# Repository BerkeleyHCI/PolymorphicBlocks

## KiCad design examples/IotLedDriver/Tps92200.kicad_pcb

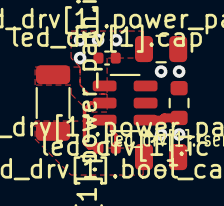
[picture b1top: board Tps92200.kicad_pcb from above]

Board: 2 copper layers, 7 parts (0 on the bottom side), 6 nets.

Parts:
led_drv[1].boot_cap: 16V 100nF X7R ±10% 0402 Multilayer Ceramic Capaci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; C_0402_1005Metric
led_drv[1].cap: 50V 100nF X7R ±10% 0402 Multilayer Ceramic Capaci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; C_0402_1005Metric
led_drv[1].ic: TPS92200D2DDCR; SOT-23-6
led_drv[1].power_path.in_cap: 50V 10uF X5R ±10% 0805 Multilayer Ceramic Capacit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; C_0805_2012Metric
led_drv[1].power_path.inductor: 980mA 4.7uH ±20% 320m? 1206 Inductors (SMD) ROHS; L_1206_3216Metric
led_drv[1].power_path.out_cap: X5R 25V ±10% 10uF 0805 Multilayer Ceramic Capacit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; C_0805_2012Metric
led_drv[1].rsense: ±1% 1/10W Thick Film Resistors 75V ±300ppm/? -55?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; R_0603_1608Metric

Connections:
Lgnd: led_drv[1].cap.2, led_drv[1].ic.3, led_drv[1].power_path.in_cap.2, led_drv[1].power_path.out_cap.2, led_drv[1].rsense.1
Lled_drv[1].boot_cap.neg: led_drv[1].boot_cap.2, led_drv[1].ic.5, led_drv[1].power_path.inductor.1
Lled_drv[1].boot_cap.pos: led_drv[1].boot_cap.1, led_drv[1].ic.6
Lled_drv[1].leda: led_drv[1].power_path.inductor.2, led_drv[1].power_path.out_cap.1
Lled_drv[1].ledk: led_drv[1].ic.1, led_drv[1].rsense.2
Lv12: led_drv[1].cap.1, led_drv[1].ic.4, led_drv[1].power_path.in_cap.1

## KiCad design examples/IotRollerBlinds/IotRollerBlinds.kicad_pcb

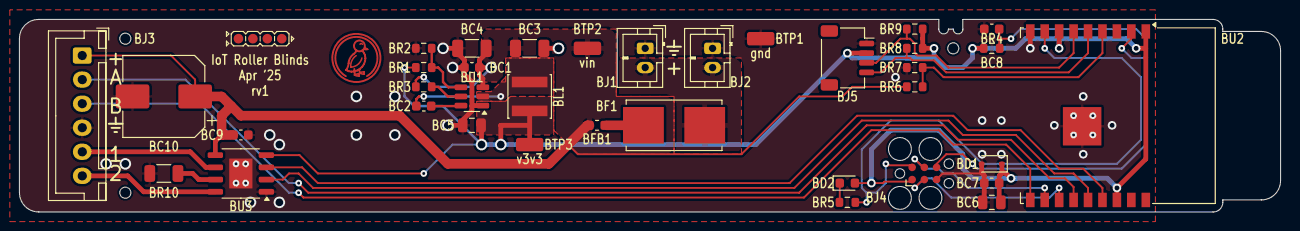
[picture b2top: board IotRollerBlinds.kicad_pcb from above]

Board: 2 copper layers, 131.0 x 20.0 mm, 40 parts (0 on the bottom side), 24 nets.

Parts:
BC1: reg_3v3.hf_in_cap; C_0603_1608Metric
BC2: reg_3v3.boot_cap; C_0603_1608Metric
BC3: reg_3v3.power_path.in_cap.c[0]; C_1206_3216Metric
BC4: reg_3v3.power_path.in_cap.c[1]; C_1206_3216Metric
BC5: reg_3v3.power_path.out_cap; C_0805_2012Metric
BC6: mcu.vcc_cap0; C_0805_2012Metric
BC7: mcu.vcc_cap1; C_0603_1608Metric
BC8: mcu.en_pull.c; C_0603_1608Metric
BC9: drv.vm_cap0; C_0603_1608Metric
BC10: drv.vm_cap1; CP_Elec_8x10
BD1: prot_3v3; D_SOD-323
BD2: ledr.package; LED_0603_1608Metric
BF1: fuse; Fuseholder_Littelfuse_Nano2_154x
BFB1: ferrite; L_0603_1608Metric
BH1: jlc_th.th1; JlcToolingHole_1.152mm
BH2: jlc_th.th2; JlcToolingHole_1.152mm
BH3: jlc_th.th3; JlcToolingHole_1.152mm
BJ1: pwr; JST_PH_B2B-PH-K_1x02_P2.00mm_Vertical
BJ2: pwr_out; JST_PH_B2B-PH-K_1x02_P2.00mm_Vertical
BJ3: conn; JST_XH_B6B-XH-A_1x06_P2.50mm_Vertical
BJ4: mcu.prog; Tag-Connect_TC2030-IDC-FP_2x03_P1.27mm_Vertical
BJ5: qwiic; JST_SH_SM04B-SRSS-TB_1x04-1MP_P1.00mm_Horizontal
BL1: reg_3v3.power_path.inductor; L_Sunlord_SWPA4030S
BR1: reg_3v3.fb.top_res; R_0603_1608Metric
BR2: reg_3v3.fb.bottom_res; R_0603_1608Metric
BR3: reg_3v3.en_res; R_0603_1608Metric
BR4: mcu.en_pull.r; R_0603_1608Metric
BR5: ledr.res; R_0603_1608Metric
BR6: vin_sense.top_res; R_0603_1608Metric
BR7: vin_sense.bottom_res; R_0603_1608Metric
BR8: qwiic_pull.scl_res; R_0603_1608Metric
BR9: qwiic_pull.sda_res; R_0603_1608Metric
BR10: drv.isen_res; R_1206_3216Metric
BTP1: gnd; TestPoint_TE_RCT_0805
BTP2: vin; TestPoint_TE_RCT_0805
BTP3: v3v3; TestPoint_TE_RCT_0805
BU1: reg_3v3.ic; SOT-23-6
BU2: mcu.ic; ESP-WROOM-02
BU3: drv.ic; HSOP-8-1EP_3.9x4.9mm_P1.27mm_EP2.41x3.1mm
duck: G***; Symbol_Duckling

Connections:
Bconn.enca: BJ3.2, BU2.13
Bconn.encb: BJ3.3, BU2.10
Bdrv.ic.isen: BR10.2, BU3.7
Bdrv.in1: BU2.15, BU3.3
Bdrv.in2: BU2.14, BU3.2
Bdrv.out1: BJ3.5, BU3.6
Bdrv.out2: BJ3.6, BU3.8
Bfuse.pwr_out: BF1.2, BFB1.1
Bgnd: BC1.2, BC3.2, BC4.2, BC5.2, BC6.2, BC7.2, BC8.2, BC9.2, BC10.2, BD1.2, BJ1.1, BJ2.1, BJ3.4, BJ4.5, BJ5.1, BR2.2, BR7.2, BR10.1, BTP1.1, BU1.1, BU2.9, BU2.19, BU3.1, BU3.9
Bledr.res.a: BD2.1, BR5.1
Bmcu.program_boot_node: BJ4.2, BR5.2, BU2.8
Bmcu.program_en_node: BC8.1, BJ4.6, BR4.2, BU2.2
Bmcu.program_uart_node.a_tx: BJ4.3, BU2.12
Bmcu.program_uart_node.b_tx: BJ4.4, BU2.11
Bqwiic_pull.i2c.scl: BJ5.4, BR8.2, BU2.5
Bqwiic_pull.i2c.sda: BJ5.3, BR9.2, BU2.6
Breg_3v3.boot_cap.neg: BC2.2, BL1.1, BU1.2
Breg_3v3.boot_cap.pos: BC2.1, BU1.6
Breg_3v3.en_res.b: BR3.2, BU1.5
Breg_3v3.fb.output: BR1.2, BR2.1, BU1.4
Bv3v3: BC5.1, BC6.1, BC7.1, BD1.1, BD2.2, BJ4.1, BJ5.2, BL1.2, BR1.1, BR4.1, BR8.1, BR9.1, BTP3.1, BU2.1, BU2.7, BU2.16, BU3.4
Bvin: BC1.1, BC3.1, BC4.1, BC9.1, BC10.1, BFB1.2, BJ3.1, BR3.1, BR6.1, BTP2.1, BU1.3, BU3.5
Bvin_raw: BF1.1, BJ1.2, BJ2.2
Bvin_sense.output: BR6.2, BR7.1, BU2.4

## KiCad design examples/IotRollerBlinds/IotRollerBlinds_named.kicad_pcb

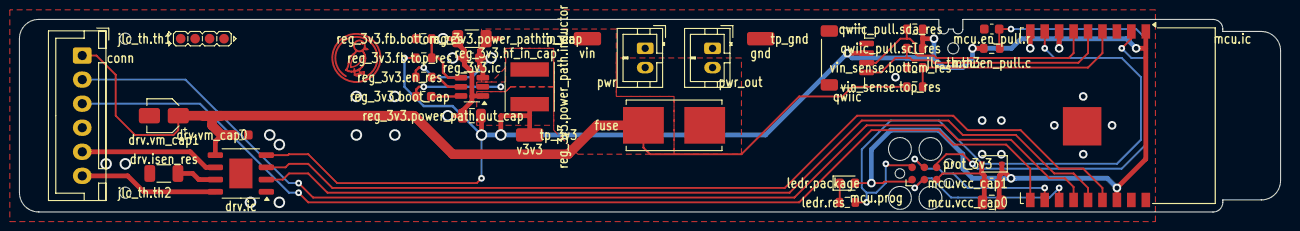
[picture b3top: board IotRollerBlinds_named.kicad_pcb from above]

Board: 2 copper layers, 131.0 x 20.0 mm, 38 parts (0 on the bottom side), 23 nets.

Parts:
conn: B6B-XH-A; JST_XH_B6B-XH-A_1x06_P2.50mm_Vertical
drv.ic: DRV8870DDAR; HSOP-8-1EP_3.9x4.9mm_P1.27mm_EP2.41x3.1mm
drv.isen_res: ±1% 1/4W Thick Film Resistors 200V ±800ppm/? -55?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; R_1206_3216Metric
drv.vm_cap0: 50V 100nF X7R ±10% 0603 Multilayer Ceramic Capaci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; C_0603_1608Metric
drv.vm_cap1: -40?~+105? 2000hrs@105? 47uF 5.4mm 35V 6.3mm ±20%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; CP_Elec_3x5.4
duck: G***; Symbol_Duckling
fuse: 01550900M; Fuseholder_Littelfuse_Nano2_154x
jlc_th.th1, jlc_th.th2, jlc_th.th3: JlcToolingHole_1.152mm
ledr.package: Red 615~630nm 1.9~2.2V 0603 Light Emitting Diodes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; LED_0603_1608Metric
ledr.res: ±1% 1/10W Thick Film Resistors 75V ±100ppm/? -55?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; R_0603_1608Metric
mcu.en_pull.c: 50V 1uF X5R ±10% 0603 Multilayer Ceramic Capacito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; C_0603_1608Metric
mcu.en_pull.r: ±1% 1/10W Thick Film Resistors 75V ±100ppm/? -55?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; R_0603_1608Metric
mcu.ic: ESP32-C3-WROOM-02; ESP-WROOM-02
mcu.prog: Tag-Connect_TC2030-IDC-FP_2x03_P1.27mm_Vertical
mcu.vcc_cap0: X5R 25V ±10% 10uF 0805 Multilayer Ceramic Capacit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; C_0805_2012Metric
mcu.vcc_cap1: 50V 100nF X7R ±10% 0603 Multilayer Ceramic Capaci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; C_0603_1608Metric
prot_3v3: 5?A@1V 90? Single 3.53V~3.67V 200mW 3.6V SOD-323 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; D_SOD-323
pwr: B2B-PH-K; JST_PH_B2B-PH-K_1x02_P2.00mm_Vertical
pwr_out: B2B-PH-K; JST_PH_B2B-PH-K_1x02_P2.00mm_Vertical
qwiic: SM04B-SRSS-TB; JST_SH_SM04B-SRSS-TB_1x04-1MP_P1.00mm_Horizontal
qwiic_pull.scl_res, qwiic_pull.sda_res: ±1% 1/10W Thick Film Resistors 75V ±100ppm/? -55?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; R_0603_1608Metric
reg_3v3.boot_cap, reg_3v3.hf_in_cap: 50V 100nF X7R ±10% 0603 Multilayer Ceramic Capaci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; C_0603_1608Metric
reg_3v3.en_res, reg_3v3.fb.bottom_res, reg_3v3.fb.top_res: ±1% 1/10W Thick Film Resistors 75V ±100ppm/? -55?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; R_0603_1608Metric
reg_3v3.ic: TPS54202H; SOT-23-6
reg_3v3.power_path.in_cap: 50V 10uF X5R ±10% 1206 Multilayer Ceramic Capacit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; C_1206_3216Metric
reg_3v3.power_path.inductor: 1.4A 22uH ±20% 126m? SMD Power Inductors ROHS; L_Taiyo-Yuden_NR-50xx
reg_3v3.power_path.out_cap: X5R 25V ±10% 10uF 0805 Multilayer Ceramic Capacit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; C_0805_2012Metric
tp_3v3: v3v3; TestPoint_TE_RCT_0805
tp_gnd: gnd; TestPoint_TE_RCT_0805
tp_vin: vin; TestPoint_TE_RCT_0805
vin_sense.bottom_res, vin_sense.top_res: ±1% 1/10W Thick Film Resistors 75V ±100ppm/? -55?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; R_0603_1608Metric

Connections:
Bconn.enca: conn.2, mcu.ic.13
Bconn.encb: conn.3, mcu.ic.10
Bdrv.ic.isen: drv.ic.7, drv.isen_res.2
Bdrv.in1: drv.ic.3, mcu.ic.15
Bdrv.in2: drv.ic.2, mcu.ic.14
Bdrv.out1: conn.5, drv.ic.6
Bdrv.out2: conn.6, drv.ic.8
Bgnd: conn.4, drv.ic.1, drv.ic.9, drv.isen_res.1, drv.vm_cap0.2, drv.vm_cap1.2, mcu.en_pull.c.2, mcu.ic.9, mcu.ic.19, mcu.prog.5, mcu.vcc_cap0.2, mcu.vcc_cap1.2, prot_3v3.2, pwr.1, pwr_out.1, qwiic.1, reg_3v3.fb.bottom_res.2, reg_3v3.hf_in_cap.2, reg_3v3.ic.1, reg_3v3.power_path.in_cap.2, reg_3v3.power_path.out_cap.2, tp_gnd.1, vin_sense.bottom_res.2
Bledr.res.a: ledr.package.1, ledr.res.1
Bmcu.program_boot_node: ledr.res.2, mcu.ic.8, mcu.prog.2
Bmcu.program_en_node: mcu.en_pull.c.1, mcu.en_pull.r.2, mcu.ic.2, mcu.prog.6
Bmcu.program_uart_node.a_tx: mcu.ic.12, mcu.prog.3
Bmcu.program_uart_node.b_tx: mcu.ic.11, mcu.prog.4
Bqwiic_pull.i2c.scl: mcu.ic.5, qwiic.4, qwiic_pull.scl_res.2
Bqwiic_pull.i2c.sda: mcu.ic.6, qwiic.3, qwiic_pull.sda_res.2
Breg_3v3.boot_cap.neg: reg_3v3.boot_cap.2, reg_3v3.ic.2, reg_3v3.power_path.inductor.1
Breg_3v3.boot_cap.pos: reg_3v3.boot_cap.1, reg_3v3.ic.6
Breg_3v3.en_res.b: reg_3v3.en_res.2, reg_3v3.ic.5
Breg_3v3.fb.output: reg_3v3.fb.bottom_res.1, reg_3v3.fb.top_res.2, reg_3v3.ic.4
Bv3v3: drv.ic.4, ledr.package.2, mcu.en_pull.r.1, mcu.ic.1, mcu.ic.7, mcu.ic.16, mcu.prog.1, mcu.vcc_cap0.1, mcu.vcc_cap1.1, prot_3v3.1, qwiic.2, qwiic_pull.scl_res.1, qwiic_pull.sda_res.1, reg_3v3.fb.top_res.1, reg_3v3.power_path.inductor.2, reg_3v3.power_path.out_cap.1, tp_3v3.1
Bvin: conn.1, drv.ic.5, drv.vm_cap0.1, drv.vm_cap1.1, fuse.2, reg_3v3.en_res.1, reg_3v3.hf_in_cap.1, reg_3v3.ic.3, reg_3v3.power_path.in_cap.1, tp_vin.1, vin_sense.top_res.1
Bvin_raw: fuse.1, pwr.2, pwr_out.2
Bvin_sense.output: mcu.ic.4, vin_sense.bottom_res.1, vin_sense.top_res.2

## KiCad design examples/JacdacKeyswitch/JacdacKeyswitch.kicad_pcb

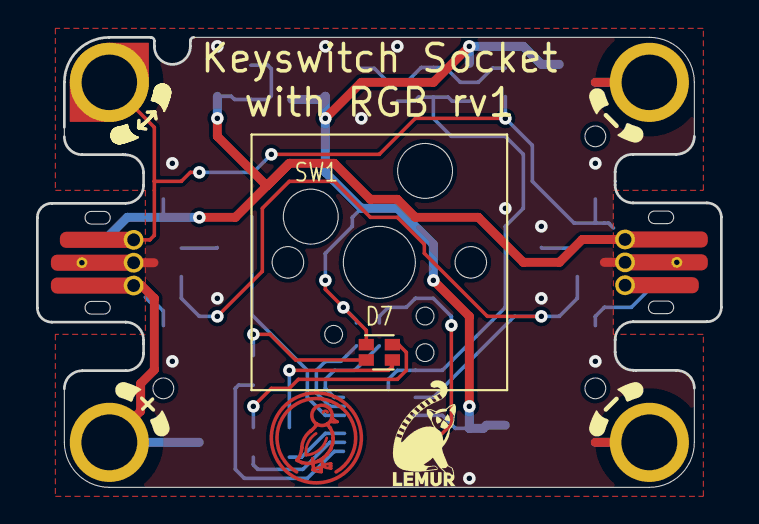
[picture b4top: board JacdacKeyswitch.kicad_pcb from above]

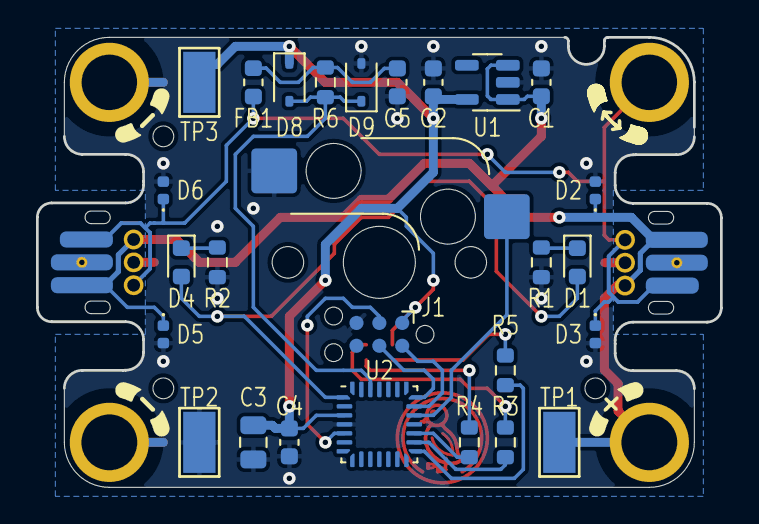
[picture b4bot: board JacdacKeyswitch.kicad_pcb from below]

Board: 2 copper layers, 38.0 x 25.0 mm, 39 parts (26 on the bottom side), 19 nets.

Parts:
C1, C2, C4, C5: C_0603_1608Metric
C3: C_0805_2012Metric
D1, D4: LED_0603_1608Metric
D2, D3, D5, D6: D_0402_1005Metric
D7: EAST1616RGBB2 (Everlight Electronics Co Ltd); LED_LiteOn_LTST-C19HE1WT
D8, D9: 1N5819WS (Guangdong Hottech) - 40V 600mV@1A 1A SO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; D_SOD-323
EC1, EC2: JD-PEC-02_Prerouted_recessed
FB1: L_0603_1608Metric
H1, H2, H3: JlcToolingHole_1.152mm
J1: Tag-Connect_TC2030-IDC-NL_2x03_P1.27mm_Vertical
MH1: jacdac_hole_DATA_notched_MH1
MH2: jacdac_hole_GND_MH2
MH3: jacdac_hole_PWR_MH3
MH4: jacdac_hole_GND_MH4
R1, R2, R3, R4, R5, R6: R_0603_1608Metric
SW1: PG151101S11 (Kailh); SW_Hotswap_Kailh_MX
TP1: 5015 (Keystone) - jd_pwr; TestPoint_Keystone_5015_Micro-Minature
TP2: 5015 (Keystone) - gnd; TestPoint_Keystone_5015_Micro-Minature
TP3: 5015 (Keystone) - v3v3; TestPoint_Keystone_5015_Micro-Minature
U1: XC6209F332MR-G (Torex Semiconductor Ltd); SOT-23-5
U2: STM32G031Gxxx (STMicroelectronics); QFN-28_4x4mm_P0.5mm
duck: G***; Symbol_Duckling
svg2mod: G***; Symbol_LemurSmall

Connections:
edge2.status_led.res.a: D4.1, R2.1
edge.status_led.res.a: D1.1, R1.1
gnd: C1.2, C2.2, C3.2, C4.2, C5.2, D2.2, D3.2, D5.2, D6.2, D9.2, EC1.2, EC2.2, J1.5, MH2.MH2, MH4.MH4, R1.2, R2.2, SW1.2, TP2.1, U1.2, U2.4
jd_data.jd_data: D3.1, D6.1, EC1.1, EC2.1, FB1.1, MH1.MH1
jd_if.ferrite.b: C5.1, FB1.2, R6.2
jd_if.signal: D8.2, D9.1, R6.1, U2.26
jd_pwr: C1.1, D2.1, D5.1, EC1.3, EC2.3, MH3.MH3, TP1.1, U1.1, U1.3
jd_status: D1.2, D4.2, U2.1
mcu.reset_node: J1.3, U2.5
mcu.swd_node.swclk: J1.4, U2.21
mcu.swd_node.swdio: J1.2, U2.20
rgb.blue_res.a: D7.1, R5.1
rgb.green_res.a: D7.4, R4.1
rgb.red_res.a: D7.3, R3.1
rgb.signals.blue: R5.2, U2.15
rgb.signals.green: R4.2, U2.17
rgb.signals.red: R3.2, U2.16
sw.out: SW1.1, U2.19
v3v3: C2.1, C3.1, C4.1, D7.2, D8.1, J1.1, TP3.1, U1.5, U2.3

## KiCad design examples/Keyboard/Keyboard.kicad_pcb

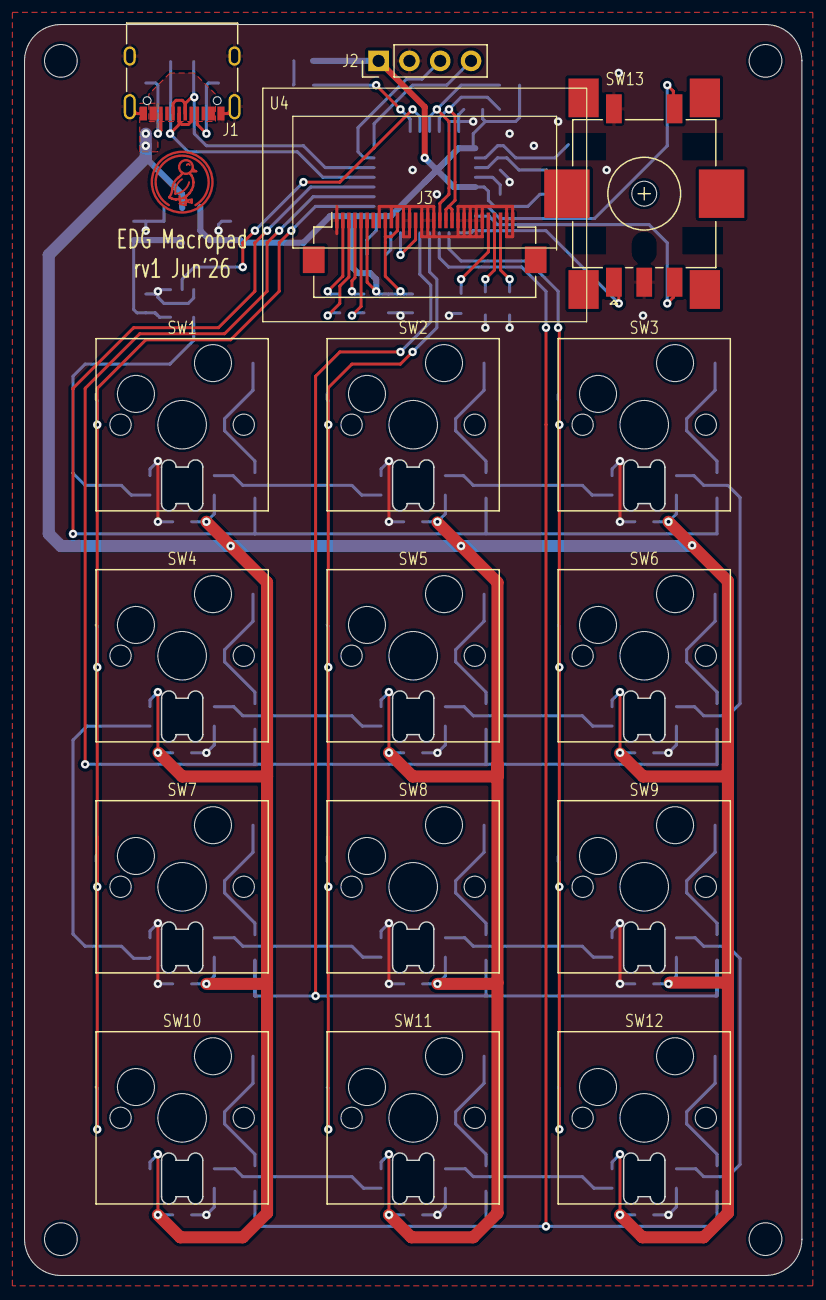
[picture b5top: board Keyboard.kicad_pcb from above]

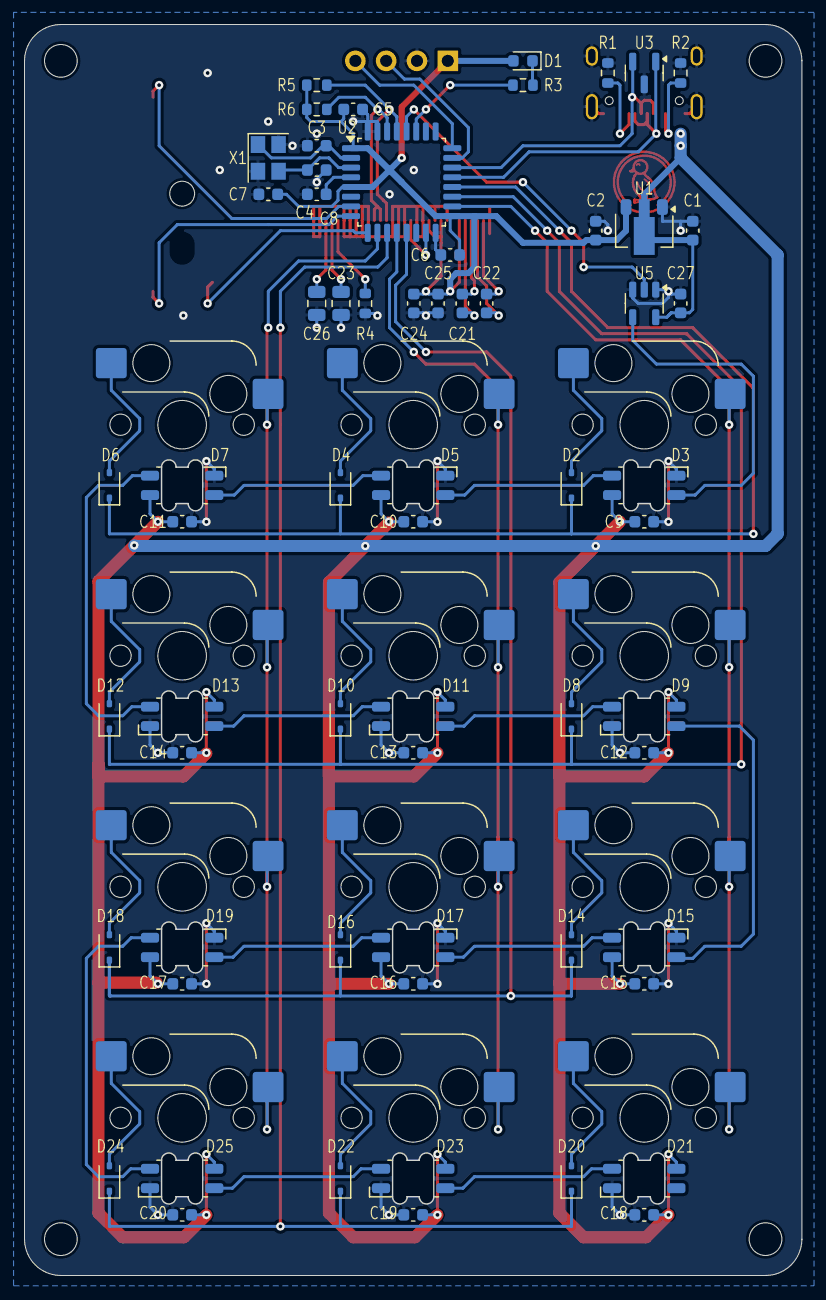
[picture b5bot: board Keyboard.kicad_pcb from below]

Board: 2 copper layers, 64.1 x 103.2 mm, 81 parts (51 on the bottom side), 59 nets.

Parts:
C1: reg.in_cap; C_0603_1608Metric
C2: reg.out_cap; C_0603_1608Metric
C3: mcu.crystal.cap_a; C_0603_1608Metric
C4: mcu.crystal.cap_b; C_0603_1608Metric
C5: mcu.vdd_cap[0]; C_0603_1608Metric
C6: mcu.vdd_cap[1]; C_0603_1608Metric
C7: mcu.vdda_cap; C_0603_1608Metric
C8: mcu.reset_cap; C_0603_1608Metric
C9: sw.sw[0,0].npx.cap; C_0603_1608Metric
C10: sw.sw[1,0].npx.cap; C_0603_1608Metric
C11: sw.sw[2,0].npx.cap; C_0603_1608Metric
C12: sw.sw[0,1].npx.cap; C_0603_1608Metric
C13: sw.sw[1,1].npx.cap; C_0603_1608Metric
C14: sw.sw[2,1].npx.cap; C_0603_1608Metric
C15: sw.sw[0,2].npx.cap; C_0603_1608Metric
C16: sw.sw[1,2].npx.cap; C_0603_1608Metric
C17: sw.sw[2,2].npx.cap; C_0603_1608Metric
C18: sw.sw[0,3].npx.cap; C_0603_1608Metric
C19: sw.sw[1,3].npx.cap; C_0603_1608Metric
C20: sw.sw[2,3].npx.cap; C_0603_1608Metric
C21: oled.c1_cap; C_0603_1608Metric
C22: oled.c2_cap; C_0603_1608Metric
C23: oled.vcomh_cap; C_0805_2012Metric
C24: oled.vdd_cap1; C_0603_1608Metric
C25: oled.vbat_cap; C_0603_1608Metric
C26: oled.vcc_cap; C_0805_2012Metric
C27: npx_shift.vdd_cap; C_0603_1608Metric
D1: ledr.package; LED_0603_1608Metric
D2: sw.sw[0,0].d; D_SOD-323
D3: sw.sw[0,0].npx.device; LED_SK6812MINI-E
D4: sw.sw[1,0].d; D_SOD-323
D5: sw.sw[1,0].npx.device; LED_SK6812MINI-E
D6: sw.sw[2,0].d; D_SOD-323
D7: sw.sw[2,0].npx.device; LED_SK6812MINI-E
D8: sw.sw[0,1].d; D_SOD-323
D9: sw.sw[0,1].npx.device; LED_SK6812MINI-E
D10: sw.sw[1,1].d; D_SOD-323
D11: sw.sw[1,1].npx.device; LED_SK6812MINI-E
D12: sw.sw[2,1].d; D_SOD-323
D13: sw.sw[2,1].npx.device; LED_SK6812MINI-E
D14: sw.sw[0,2].d; D_SOD-323
D15: sw.sw[0,2].npx.device; LED_SK6812MINI-E
D16: sw.sw[1,2].d; D_SOD-323
D17: sw.sw[1,2].npx.device; LED_SK6812MINI-E
D18: sw.sw[2,2].d; D_SOD-323
D19: sw.sw[2,2].npx.device; LED_SK6812MINI-E
D20: sw.sw[0,3].d; D_SOD-323
D21: sw.sw[0,3].npx.device; LED_SK6812MINI-E
D22: sw.sw[1,3].d; D_SOD-323
D23: sw.sw[1,3].npx.device; LED_SK6812MINI-E
D24: sw.sw[2,3].d; D_SOD-323
D25: sw.sw[2,3].npx.device; LED_SK6812MINI-E
J1: usb.conn; USB_C_Receptacle_XKB_U262-16XN-4BVC11
J2: mcu.sdi; PinHeader_1x04_P2.54mm_Vertical
J3: oled.device; Hirose_FH12-30S-0.5SH_1x30-1MP_P0.50mm_Horizontal
R1: usb.cc_pull.cc1; R_0603_1608Metric
R2: usb.cc_pull.cc2; R_0603_1608Metric
R3: ledr.res; R_0603_1608Metric
R4: oled.iref_res; R_0603_1608Metric
R5: i2c_pull.scl_res; R_0603_1608Metric
R6: i2c_pull.sda_res; R_0603_1608Metric
SW1: sw.sw[0,0].sw; SW_Hotswap_Kailh_MX
SW2: sw.sw[1,0].sw; SW_Hotswap_Kailh_MX
SW3: sw.sw[2,0].sw; SW_Hotswap_Kailh_MX
SW4: sw.sw[0,1].sw; SW_Hotswap_Kailh_MX
SW5: sw.sw[1,1].sw; SW_Hotswap_Kailh_MX
SW6: sw.sw[2,1].sw; SW_Hotswap_Kailh_MX
SW7: sw.sw[0,2].sw; SW_Hotswap_Kailh_MX
SW8: sw.sw[1,2].sw; SW_Hotswap_Kailh_MX
SW9: sw.sw[2,2].sw; SW_Hotswap_Kailh_MX
SW10: sw.sw[0,3].sw; SW_Hotswap_Kailh_MX
SW11: sw.sw[1,3].sw; SW_Hotswap_Kailh_MX
SW12: sw.sw[2,3].sw; SW_Hotswap_Kailh_MX
SW13: enc; RotaryEncoder_Bourns_PEC11S
U1: reg.ic; SOT-89-3
U2: mcu.ic; LQFP-32_7x7mm_P0.8mm
U3: usb_esd; SOT-23
U4: oled.lcd; Lcd_Er_Oled0.96_1.1_Outline
U5: npx_shift.ic; SOT-23-5
X1: mcu.crystal.package; Crystal_SMD_3225-4Pin_3.2x2.5mm
duck: G***; Symbol_Duckling

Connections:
enc.a: SW13.A, U2.9
enc.b: SW13.B, U2.8
enc.sw: SW13.S1, U2.7
ledr.package.k: D1.1, R3.1
ledr.signal: R3.2, U2.27
mcu.gpio.sw_col_0: SW1.1, SW4.1, SW7.1, SW10.1, U2.18
mcu.gpio.sw_col_1: SW2.1, SW5.1, SW8.1, SW11.1, U2.12
mcu.gpio.sw_col_2: SW3.1, SW6.1, SW9.1, SW12.1, U2.10
mcu.gpio.sw_row_0: D2.1, D4.1, D6.1, U2.20
mcu.gpio.sw_row_1: D8.1, D10.1, D12.1, U2.19
mcu.gpio.sw_row_2: D14.1, D16.1, D18.1, U2.13
mcu.gpio.sw_row_3: D20.1, D22.1, D24.1, U2.11
mcu.ic.nrst: C8.1, U2.4
mcu.ic.swclk: J2.4, U2.24
mcu.ic.swdio: J2.3, U2.23
mcu.xtal_node.xi: C3.1, U2.2, X1.1
mcu.xtal_node.xo: C4.1, U2.3, X1.3
npx_shift.input: U2.28, U5.2
oled.device.c1n: C21.2, J3.5
oled.device.c1p: C21.1, J3.4
oled.device.c2n: C22.2, J3.3
oled.device.c2p: C22.1, J3.2
oled.device.iref: J3.26, R4.2
oled.device.vcc: C26.1, J3.28
oled.device.vcomh: C23.1, J3.27
oled.i2c.scl: J3.18, R5.2, U2.29
oled.i2c.sda: J3.19, J3.20, R6.2, U2.30
oled.reset: J3.14, U2.15
reg.pwr_out: C2.1, C5.1, C6.1, C7.1, C24.1, C25.1, D1.2, J2.1, J3.6, J3.9, J3.11, R5.1, R6.1, U1.3, U2.1, U2.5, U2.17
sw.npx_din: D3.4, U5.4
sw.sw[0,0].npx_dout: D3.2, D5.4
sw.sw[0,0].sw.com: D2.2, SW1.2
sw.sw[0,1].npx_din: D9.4, D11.2
sw.sw[0,1].npx_dout: D9.2, D15.4
sw.sw[0,1].sw.com: D8.2, SW4.2
sw.sw[0,2].npx_dout: D15.2, D17.4
sw.sw[0,2].sw.com: D14.2, SW7.2
sw.sw[0,3].npx_din: D21.4, D23.2
sw.sw[0,3].sw.com: D20.2, SW10.2
sw.sw[1,0].npx_dout: D5.2, D7.4
sw.sw[1,0].sw.com: D4.2, SW2.2
sw.sw[1,1].npx_din: D11.4, D13.2
sw.sw[1,1].sw.com: D10.2, SW5.2
sw.sw[1,2].npx_dout: D17.2, D19.4
sw.sw[1,2].sw.com: D16.2, SW8.2
sw.sw[1,3].npx_din: D23.4, D25.2
sw.sw[1,3].sw.com: D22.2, SW11.2
sw.sw[2,0].npx_dout: D7.2, D13.4
sw.sw[2,0].sw.com: D6.2, SW3.2
sw.sw[2,1].sw.com: D12.2, SW6.2
sw.sw[2,2].npx_dout: D19.2, D25.4
sw.sw[2,2].sw.com: D18.2, SW9.2
sw.sw[2,3].sw.com: D24.2, SW12.2
usb.conn.cc.cc1: J1.A5, R1.2
usb.conn.cc.cc2: J1.B5, R2.2
usb.gnd: C1.2, C2.2, C3.2, C4.2, C5.2, C6.2, C7.2, C8.2, C9.2, C10.2, C11.2, C12.2, C13.2, C14.2, C15.2, C16.2, C17.2, C18.2, C19.2, C20.2, C23.2, C24.2, C25.2, C26.2, C27.2, D3.3, D5.3, D7.3, D9.3, D11.3, D13.3, D15.3, D17.3, D19.3, D21.3, D23.3, D25.3, J1.A1, J1.A12, J1.B1, J1.B12, J1.S1, J2.2, J3.1, J3.8, J3.10, J3.12, J3.13, J3.15, J3.16, J3.17, J3.21, J3.22, J3.23, J3.24, J3.25, J3.29, J3.30, R1.1, R2.1, R4.1, SW13.C, SW13.S2, U1.1, U2.16, U2.31, U2.32, U3.3, U5.1, U5.3, X1.2, X1.4
usb.pwr: C1.1, C9.1, C10.1, C11.1, C12.1, C13.1, C14.1, C15.1, C16.1, C17.1, C18.1, C19.1, C20.1, C27.1, D3.1, D5.1, D7.1, D9.1, D11.1, D13.1, D15.1, D17.1, D19.1, D21.1, D23.1, D25.1, J1.A4, J1.A9, J1.B4, J1.B9, U1.2, U5.5
usb.usb.dm: J1.A7, J1.B7, U2.21, U3.1
usb.usb.dp: J1.A6, J1.B6, U2.22, U3.2

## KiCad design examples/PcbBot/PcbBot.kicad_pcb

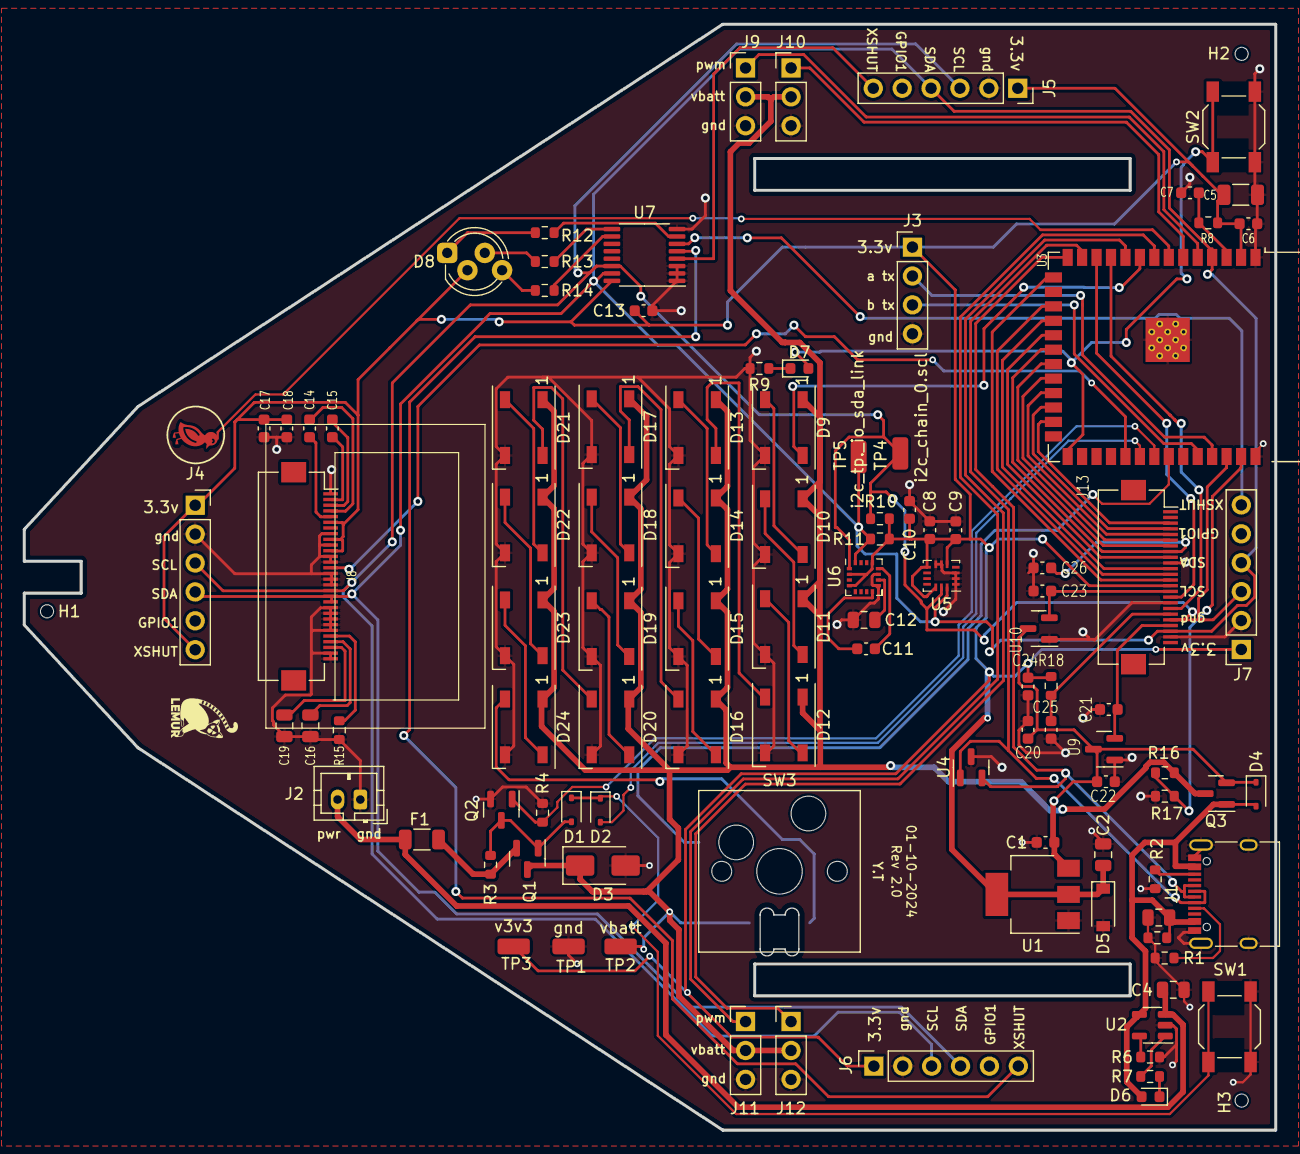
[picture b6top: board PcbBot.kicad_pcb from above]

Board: 2 copper layers, 110.0 x 97.2 mm, 109 parts (0 on the bottom side), 83 nets.

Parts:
C1, C6, C7, C8, C9, C10, C11, C13, C14, C15, C17, C18, C20, C21, C22, C23, C24, C25, C26: C_0603_1608Metric
C2, C3, C4, C12, C16, C19: C_0805_2012Metric
C5: C_1206_3216Metric
D1, D2: 30V 370mV@1mA 30mA SOD-323 Schottky Barrier Diode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; D_SOD-323
D3: 10?A@2V 5? Single 5.32V~5.92V 1W 5.6V SMAF Zener 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; D_SMA
D4: 40V 600mV@1A 1A SOD-323 Schottky Barrier Diodes (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; D_SOD-323
D5: 5?A@1V 90? Single 3.6V~3.8V 350mW 3.4V SOD-123 Ze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; D_SOD-123
D6: LED_0603_1608Metric
D7: Red 615~630nm 1.9~2.2V 0603 Light Emitting Diodes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; LED_0603_1608Metric
D8: COM-09264; LED_D5.0mm-4_RGB_Staggered_Pins
D9, D10, D11, D12, D13, D14, D15, D16, D17, D18, D19, D20, D21, D22, D23, D24: WS2812B; LED_WS2812B_PLCC4_5.0x5.0mm_P3.2mm
D25: SK6812MINI-E; LED_SK6812MINI-E
F1: 6V 2A 100A 4A 1206 Resettable Fuses ROHS; R_1206_3216Metric
H1, H2, H3: JlcToolingHole_1.152mm
J1: COM-15111; USB_C_Receptacle_XKB_U262-16XN-4BVC11
J2: B2B-PH-K; JST_PH_B2B-PH-K_1x02_P2.00mm_Vertical
J3: PinHeader2.54 1x4; PinHeader_1x04_P2.54mm_Vertical
J4, J5, J6, J7: PinSocket2.54 1x6; PinSocket_1x06_P2.54mm_Vertical
J8: AFC01-S30FCA-00; Hirose_FH12-30S-0.5SH_1x30-1MP_P0.50mm_Horizontal
J9, J10, J11, J12: PinHeader2.54 1x3; PinHeader_1x03_P2.54mm_Vertical
J13: AFC01-S24FCA-00; Hirose_FH12-24S-0.5SH_1x24-1MP_P0.50mm_Horizontal
Q1: 20V 3.1A 860mW 112m?@4.5V,2.8A 1V@250?A P Channel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; SOT-23
Q2: 60V 115mA 200mW 7.5?@10V,500mA 2.5V@250?A N Chann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; SOT-23
Q3: 30V 4A 44m?@10V,4.3A 1.4W 1.3V@250?A P Channel SO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; SOT-23
R1, R2, R3, R4, R5, R6, R7, R8, R9, R10, R11, R12, R13, R14, R15, R16, R17, R18: R_0603_1608Metric
SW1, SW2: 5.1mm switch; SW_SPST_SKQG_WithoutStem
SW3: PG151101S11; SW_Hotswap_Kailh_MX
TP1: gnd; TestPoint_TE_RCT_0805
TP2: vbatt; TestPoint_TE_RCT_0805
TP3: v3v3; TestPoint_TE_RCT_0805
TP4: i2c_chain_0.scl; TestPoint_TE_RCT_0805
TP5: i2c_tp._io_sda_link; TestPoint_TE_RCT_0805
U1: LDL1117S33R; SOT-223-3_TabPin2
U2: MCP73831T-2ACI/OT; SOT-23-5
U3: ESP32-S3-WROOM-1-N16R8; ESP32-S3-WROOM-1
U4: PESD5V0X1BT; SOT-23
U5: LSM6DS3TR-C; Bosch_LGA-14_3x2.5mm_P0.5mm
U6: QMC5883L; LGA-16_3x3mm_P0.5mm
U7: PCA9554APW,118; TSSOP-16_4.4x5mm_P0.65mm
U8: ER-OLED-0.96-1.1; Lcd_Er_Oled0.96_1.1_Outline
U9: XC6206P252MR; SOT-23
U10: XC6206P122MR-G; SOT-23
svg2mod: G***; Symbol_LemurSmall
svg2mod#2: G***; Symbol_DucklingSolid

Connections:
batt.pwr: C4.1, F1.1, J2.2, U2.3
batt_sense.output: R16.2, R17.1, U3.39
cam.device.reset: C25.1, J13.19, R18.2
cam.dvp8.href: J13.16, U3.12
cam.dvp8.pclk: C26.1, J13.8, U3.20
cam.dvp8.vsync: J13.18, U3.11
cam.dvp8.xclk: J13.12, U3.17
cam.dvp8.y0: J13.6, U3.22
cam.dvp8.y1: J13.4, U3.24
cam.dvp8.y2: J13.3, U3.25
cam.dvp8.y3: J13.5, U3.23
cam.dvp8.y4: J13.7, U3.21
cam.dvp8.y5: J13.9, U3.19
cam.dvp8.y6: J13.11, U3.18
cam.dvp8.y7: J13.13, U3.15
charge_led.res.a: D6.1, R7.1
charge_led.signal: R7.2, U2.1
charger.prog_res.a: R6.1, U2.5
expander.io.rgb_blue: R14.2, U7.10
expander.io.rgb_green: R13.2, U7.9
expander.io.rgb_red: R12.2, U7.7
expander.io.tof_xshut_1: J5.6, U7.4
expander.io.tof_xshut_2: J6.6, U7.5
expander.io.tof_xshut_3: J7.6, U7.6
fuse.pwr_out: F1.2, Q1.2, R3.1
gate.btn_out: D2.2, U3.32
gate.control: Q2.1, R4.2, U3.33
gate.ctl_diode.cathode: D1.1, D2.1, SW1.1
gate.pull_res.b: D1.2, Q1.1, Q2.3, R3.2
gnd: C1.2, C2.2, C3.2, C4.2, C5.2, C6.2, C7.2, C8.2, C9.2, C10.2, C12.2, C13.2, C16.2, C17.2, C18.2, C19.2, C20.2, C21.2, C22.2, C23.2, C24.2, C25.2, C26.2, D3.2, D5.2, D9.3, D10.3, D11.3, D12.3, D13.3, D14.3, D15.3, D16.3, D17.3, D18.3, D19.3, D20.3, D21.3, D22.3, D23.3, D24.3, D25.3, J1.A1, J1.A12, J1.B1, J1.B12, J1.S1, J2.1, J3.4, J4.2, J5.2, J6.2, J7.2, J8.1, J8.8, J8.10, J8.12, J8.13, J8.15, J8.16, J8.17, J8.21, J8.22, J8.23, J8.24, J8.25, J8.29, J8.30, J9.3, J10.3, J11.3, J12.3, J13.10, J13.17, J13.23, Q2.2, R1.1, R2.1, R4.1, R5.2, R6.2, R9.2, R15.2, R17.2, SW1.2, SW2.2, SW3.2, TP1.1, U1.1, U2.2, U3.1, U3.40, U3.41, U4.3, U5.1, U5.2, U5.3, U5.6, U5.7, U6.9, U6.11, U7.1, U7.2, U7.3, U7.8, U9.1, U10.1
i2c_chain_0.scl: J4.3, J5.3, J6.3, J7.3, J8.18, J13.20, R10.2, TP4.1, U3.38, U5.13, U6.1, U7.14
i2c_chain_0.sda: J4.4, J5.4, J6.4, J7.4, J8.19, J8.20, J13.22, R11.2, TP5.1, U3.4, U5.14, U6.16, U7.15
led.res.a: D7.1, R9.1
mag.c1.pos: C12.1, U6.10
mag.set_cap.neg: C11.2, U6.12
mag.set_cap.pos: C11.1, U6.8
mcu.program_boot_node: D7.2, SW2.1, U3.27
mcu.program_en_node: C7.1, R8.2, U3.3
mcu.program_uart_node.a_tx: J3.2, U3.37
mcu.program_uart_node.b_tx: J3.3, U3.36
npx.din: D9.4, U3.9
npx.dout: D24.2, D25.4
npx.led[0].dout: D9.2, D10.4
npx.led[1].dout: D10.2, D11.4
npx.led[2].dout: D11.2, D12.4
npx.led[3].dout: D12.2, D13.4
npx.led[4].dout: D13.2, D14.4
npx.led[5].dout: D14.2, D15.4
npx.led[6].dout: D15.2, D16.4
npx.led[7].dout: D16.2, D17.4
npx.led[8].dout: D17.2, D18.4
npx.led[9].dout: D18.2, D19.4
npx.led[10].dout: D19.2, D20.4
npx.led[11].dout: D20.2, D21.4
npx.led[12].dout: D21.2, D22.4
npx.led[13].dout: D22.2, D23.4
npx.led[14].dout: D23.2, D24.4
oled.c1_cap.neg: C14.2, J8.5
oled.c1_cap.pos: C14.1, J8.4
oled.c2_cap.neg: C15.2, J8.3
oled.c2_cap.pos: C15.1, J8.2
oled.device.vcc: C19.1, J8.28
oled.device.vcomh: C16.1, J8.27
oled.iref_res.a: J8.26, R15.1
oled.reset: J8.14, U3.31
pwr: C1.1, C20.1, C22.1, D4.1, Q3.2, U1.3, U9.3, U10.3
rgb.blue_res.a: D8.4, R14.1
rgb.green_res.a: D8.3, R13.1
rgb.red_res.a: D8.1, R12.1
servo[0].pwm: J9.1, U3.5
servo[1].pwm: J10.1, U3.6
servo[2].pwm: J11.1, U3.8
servo[3].pwm: J12.1, U3.10
switch.out: SW3.1, U3.34
usb.conn.A5: J1.A5, R1.2
usb.conn.B5: J1.B5, R2.2
usb_chain_0.d_N: J1.A7, J1.B7, U3.13, U4.1
usb_chain_0.d_P: J1.A6, J1.B6, U3.14, U4.2
v1v2: C23.1, J13.15, U10.2
v2v5: C21.1, J13.21, U9.2
v3v3: C2.1, C5.1, C6.1, C8.1, C9.1, C10.1, C13.1, C17.1, C18.1, C24.1, D5.1, D8.2, J3.1, J4.1, J4.6, J5.1, J6.1, J7.1, J8.6, J8.9, J8.11, J13.14, R8.1, R10.1, R11.1, R18.1, TP3.1, U1.2, U3.2, U5.5, U5.8, U5.12, U6.2, U6.4, U6.13, U7.16
vbatt: D3.1, D9.1, D10.1, D11.1, D12.1, D13.1, D14.1, D15.1, D16.1, D17.1, D18.1, D19.1, D20.1, D21.1, D22.1, D23.1, D24.1, D25.1, J9.2, J10.2, J11.2, J12.2, Q1.3, Q3.3, R16.1, TP2.1
vusb: C3.1, D4.2, D6.2, J1.A4, J1.A9, J1.B4, J1.B9, Q3.1, R5.1, U2.4

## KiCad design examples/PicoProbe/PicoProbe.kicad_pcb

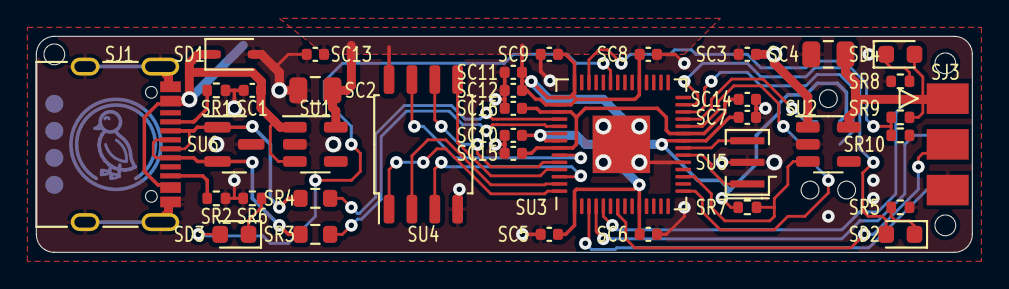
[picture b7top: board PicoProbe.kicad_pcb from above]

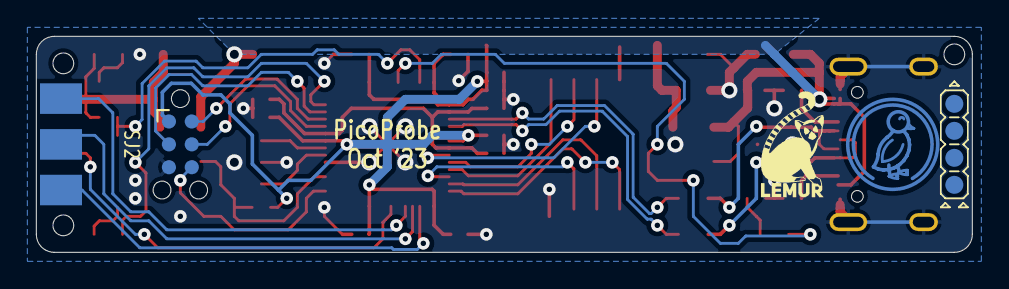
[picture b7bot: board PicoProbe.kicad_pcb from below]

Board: 2 copper layers, 52.0 x 12.0 mm, 45 parts (4 on the bottom side), 34 nets.

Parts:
SC1, SC3, SC5, SC6, SC7, SC8, SC9, SC10, SC11, SC12, SC13, SC14, SC15, SC16: C_0402_1005Metric
SC2, SC4: C_0805_2012Metric
SD1: BZT52-B5V6S_R1_00001 (PANJIT International) - 100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; D_SOD-323
SD2, SD4: LED_0603_1608Metric
SD3: C2290 (Hubei KENTO Elec) - White 0603 Light Emitt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; LED_0603_1608Metric
SH1, SH2, SH3: JlcToolingHole_1.152mm
SJ1: COM-15111 (Sparkfun); USB_C_Receptacle_XKB_U262-16XN-4BVC11
SJ2: Tag-Connect_TC2030-IDC-NL_2x03_P1.27mm_Vertical
SJ3: PinHeader2.54 Shrouded 2x3 (Generic); PinHeader_2x03_P2.54mm_EdgeInline
SR1, SR2, SR5, SR6, SR7, SR8, SR9, SR10: R_0402_1005Metric
SR3, SR4: R_0603_1608Metric
SU1, SU2: AP2204K-3.3 (Diodes Incorporated); SOT-23-5
SU3: RP2040 (Raspberry Pi); QFN-56-1EP_7x7mm_P0.4mm_EP3.2x3.2mm
SU4: W25Q128JVSIQ (Winbond Electronics); SOIC-8_5.23x5.23mm_P1.27mm
SU5: CSTNE12M0GH5L000R0 (Murata Electronics); Resonator_SMD_Murata_CSTxExxV-3Pin_3.0x1.1mm
SU6: PESD5V0X1BT (Nexperia); SOT-23
UU4: Duck; Symbol_Duckling
UU5: Lemur; Symbol_LemurSmall
UU6: IdDots4; Indicator_IdDots_4

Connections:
Sen_pull.io: SR7.2, SU2.3, SU3.17
Sgnd: SC1.2, SC2.2, SC3.2, SC4.2, SC5.2, SC6.2, SC7.2, SC8.2, SC9.2, SC10.2, SC11.2, SC12.2, SC13.2, SC14.2, SC15.2, SC16.2, SD1.2, SJ1.A1, SJ1.A12, SJ1.B1, SJ1.B12, SJ1.S1, SJ2.5, SJ3.5, SR1.1, SR2.1, SR5.2, SR6.2, SR8.2, SR10.2, SU1.2, SU2.2, SU3.19, SU3.57, SU4.4, SU5.2, SU6.3
Sled_target.res.a: SD4.1, SR8.1
Sled_tgt.res.a: SD2.1, SR5.1
Sled_tgt.signal: SD2.2, SU3.27
Sled_usb.res.a: SD3.1, SR6.1
Sled_usb.signal: SD3.2, SU3.37
Smcu.ic.qspi.miso: SU3.55, SU4.2
Smcu.ic.qspi.mosi: SU3.53, SU4.5
Smcu.ic.qspi.sck: SU3.52, SU4.6
Smcu.ic.qspi_cs: SU3.56, SU4.1
Smcu.ic.qspi_sd2: SU3.54, SU4.3
Smcu.ic.qspi_sd3: SU3.51, SU4.7
Smcu.ic.vreg_vout: SC14.1, SC15.1, SC16.1, SU3.23, SU3.45, SU3.50
Smcu.reset_node: SJ2.3, SU3.26
Smcu.swd.swo: SJ2.6, SU3.15
Smcu.swd_node.swclk: SJ2.4, SU3.24
Smcu.swd_node.swdio: SJ2.2, SU3.25
Smcu.usb_chain_0.d_N: SR4.1, SU3.46
Smcu.usb_chain_0.d_P: SR3.1, SU3.47
Smcu.xtal_node.driver.xtal_in: SU3.20, SU5.1
Smcu.xtal_node.driver.xtal_out: SU3.21, SU5.3
Starget.reset: SJ3.3, SU3.7
Starget.swo: SJ3.6, SU3.3
Starget_drv.swclk: SJ3.4, SU3.4
Starget_drv.swdio: SJ3.2, SU3.5
Starget_sense.output: SR9.2, SR10.1, SU3.40
Susb.conn.A5: SJ1.A5, SR1.2
Susb.conn.B5: SJ1.B5, SR2.2
Susb_chain_0.d_N: SJ1.A7, SJ1.B7, SR4.2, SU6.1
Susb_chain_0.d_P: SJ1.A6, SJ1.B6, SR3.2, SU6.2
Sv3v3: SC2.1, SC5.1, SC6.1, SC7.1, SC8.1, SC9.1, SC10.1, SC11.1, SC12.1, SC13.1, SJ2.1, SR7.1, SU1.5, SU3.1, SU3.10, SU3.22, SU3.33, SU3.42, SU3.43, SU3.44, SU3.48, SU3.49, SU4.8
Svtarget: SC4.1, SD4.2, SJ3.1, SR9.1, SU2.5
Svusb: SC1.1, SC3.1, SD1.1, SJ1.A4, SJ1.A9, SJ1.B4, SJ1.B9, SU1.1, SU1.3, SU2.1

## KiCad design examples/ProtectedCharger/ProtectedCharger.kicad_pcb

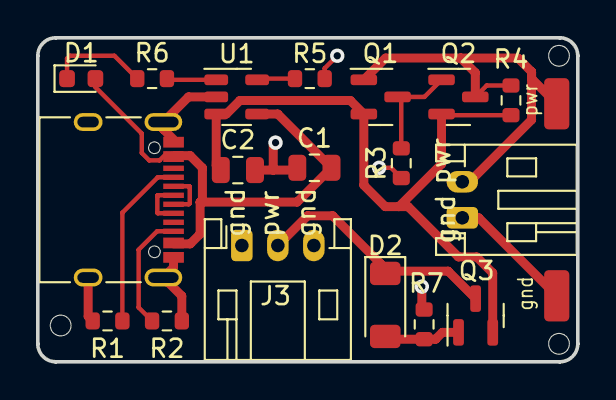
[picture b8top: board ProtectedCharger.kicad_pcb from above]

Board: 2 copper layers, 30.0 x 18.0 mm, 24 parts (1 on the bottom side), 14 nets.

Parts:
C1, C2: C_0805_2012Metric
D1: LED_0603_1608Metric
D2: 2?A@1V 85? Single 3.1V~3.5V 500mW 3.3V LL-34 Zene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; D_MiniMELF
H1, H2, H3: JlcToolingHole_1.152mm
J1: COM-15111; USB_C_Receptacle_XKB_U262-16XN-4BVC11
J2: S2B-PH-K; JST_PH_S2B-PH-K_1x02_P2.00mm_Horizontal
J3: S3B-PH-K; JST_PH_S3B-PH-K_1x03_P2.00mm_Horizontal
Q1: 30V 4A 44m?@10V,4.3A 1.4W 1.3V@250?A P Channel SO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; SOT-23
Q2: 60V 5.2A 50m?@10V,3.2A 27W 2.5V@250?A P Channel S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; SOT-23
Q3: 20V 3.1A 860mW 112m?@4.5V,2.8A 1V@250?A P Channel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; SOT-23
R1, R2, R3, R4, R5, R6, R7: R_0603_1608Metric
TP1: gnd; TestPoint_TE_RCT_0805
TP2: _batt_pwr_link; TestPoint_TE_RCT_0805
U1: MCP73831T-2ACI/OT; SOT-23-5
svg2mod: G***; Symbol_DucklingSolid

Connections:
(adapter)pwr_pins.pins.2.src: D2.1, J3.2, Q3.3
batt.pwr: J2.2, Q1.1, Q2.3, R4.2, TP2.1
charge_led.res.a: D1.1, R6.1
charge_led.signal: R6.2, U1.1
charger.prog_res.a: R5.1, U1.5
charger.pwr_bat: C2.1, Q1.2, Q2.2, Q3.2, R4.1, U1.3
gnd: C1.2, C2.2, J1.A1, J1.A12, J1.B1, J1.B12, J1.S1, J2.1, J3.1, J3.3, R1.1, R2.1, R3.2, R5.2, R7.2, TP1.1, U1.2
pmos.r1.a: Q1.3, Q2.1, R3.1
pmos_load.fet.gate: D2.2, Q3.1, R7.1
usb.conn.A5: J1.A5, R1.2
usb.conn.B5: J1.B5, R2.2
usb.usb.dm: J1.A7, J1.B7
usb.usb.dp: J1.A6, J1.B6
vusb: C1.1, D1.2, J1.A4, J1.A9, J1.B4, J1.B9, U1.4
